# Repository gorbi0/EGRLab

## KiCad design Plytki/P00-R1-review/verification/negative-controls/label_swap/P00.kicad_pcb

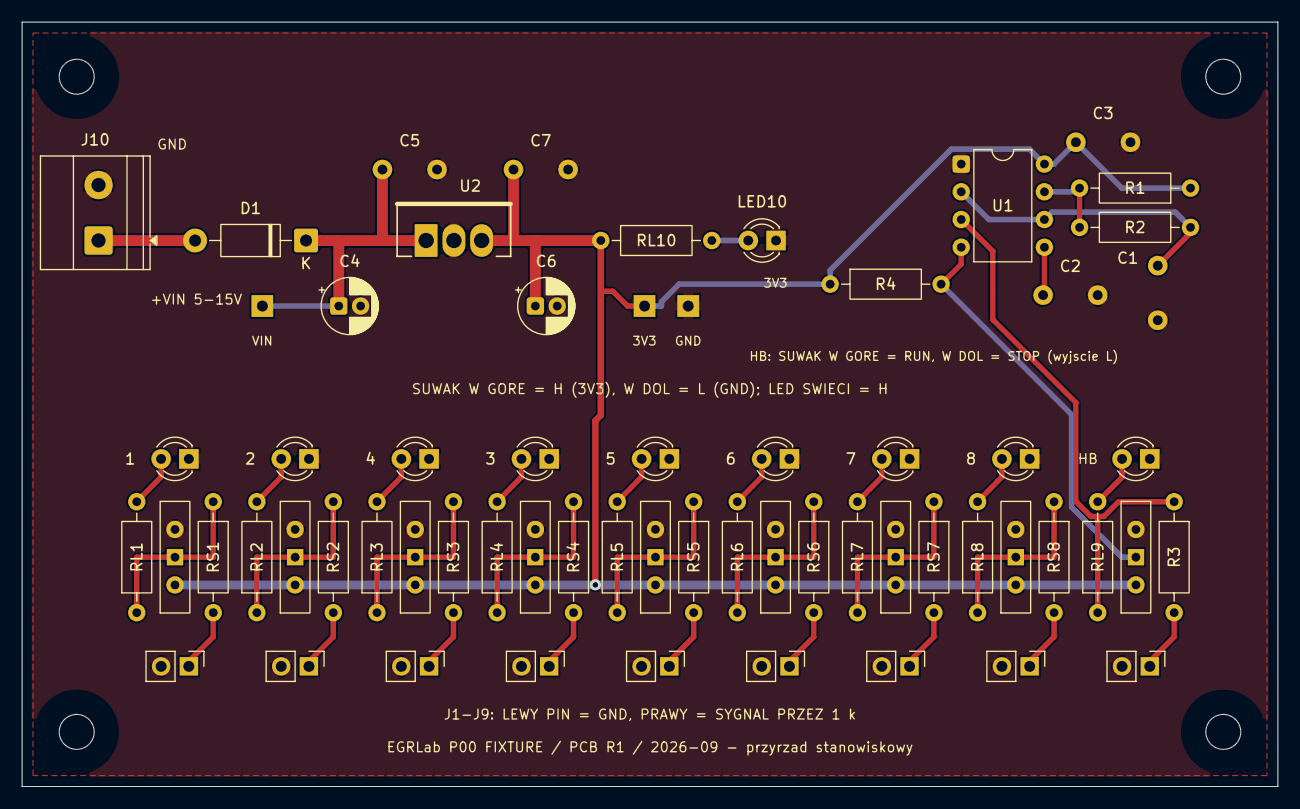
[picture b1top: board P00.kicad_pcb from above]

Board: 2 copper layers, 115.0 x 70.0 mm, 68 parts (0 on the bottom side), 36 nets.

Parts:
C1, C3, C5, C7: 100nF / X7R; C_Vishay_K15_H5_P5
C2: 10nF / X7R; C_Vishay_K15_H5_P5
C4: 10u / 50V; CP_Radial_D5.0mm_P2.00mm
C6: 22u / 16V; CP_Radial_D5.0mm_P2.00mm
D1: 1N5819; D_DO-41_SOD81_P10.16mm_Horizontal
H1, H2, H3, H4: M3 NPTH
J1: CH1 / pin header 1x2; PinHeader_1x02_P2.54mm_Vertical
J2: CH2 / pin header 1x2; PinHeader_1x02_P2.54mm_Vertical
J3: CH3 / pin header 1x2; PinHeader_1x02_P2.54mm_Vertical
J4: CH4 / pin header 1x2; PinHeader_1x02_P2.54mm_Vertical
J5: CH5 / pin header 1x2; PinHeader_1x02_P2.54mm_Vertical
J6: CH6 / pin header 1x2; PinHeader_1x02_P2.54mm_Vertical
J7: CH7 / pin header 1x2; PinHeader_1x02_P2.54mm_Vertical
J8: CH8 / pin header 1x2; PinHeader_1x02_P2.54mm_Vertical
J9: HEART / pin header 1x2; PinHeader_1x02_P2.54mm_Vertical
J10: VIN 5-15V / MKDS 2p; TerminalBlock_Phoenix_MKDS-1,5-2-5.08_1x02_P5.08mm_Horizont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
LED1: GREEN 3mm / CH1; LED_D3.0mm
LED2: GREEN 3mm / CH2; LED_D3.0mm
LED3: GREEN 3mm / CH3; LED_D3.0mm
LED4: GREEN 3mm / CH4; LED_D3.0mm
LED5: GREEN 3mm / CH5; LED_D3.0mm
LED6: GREEN 3mm / CH6; LED_D3.0mm
LED7: GREEN 3mm / CH7; LED_D3.0mm
LED8: GREEN 3mm / CH8; LED_D3.0mm
LED9: YELLOW 3mm / HEART; LED_D3.0mm
LED10: RED 3mm / 3V3; LED_D3.0mm
R1: 4K7 / 1%; R_Axial_DIN0207_L6.3mm_D2.5mm_P10.16mm_Horizontal
R2: 68K / 1%; R_Axial_DIN0207_L6.3mm_D2.5mm_P10.16mm_Horizontal
R3: 1K / 1%; R_Axial_DIN0207_L6.3mm_D2.5mm_P10.16mm_Horizontal
R4: 100K / 1%; R_Axial_DIN0207_L6.3mm_D2.5mm_P10.16mm_Horizontal
RL1, RL2, RL3, RL4, RL5, RL6, RL7, RL8, RL9, RL10: 1K / 1%; R_Axial_DIN0207_L6.3mm_D2.5mm_P10.16mm_Horizontal
RS1, RS2, RS3, RS4, RS5, RS6, RS7, RS8: 1K / 1%; R_Axial_DIN0207_L6.3mm_D2.5mm_P10.16mm_Horizontal
SW1: CH1 H/L; SW_Slide-03_Wuerth-WS-SLTV_10x2.5x6.4_P2.54mm
SW2: CH2 H/L; SW_Slide-03_Wuerth-WS-SLTV_10x2.5x6.4_P2.54mm
SW3: CH3 H/L; SW_Slide-03_Wuerth-WS-SLTV_10x2.5x6.4_P2.54mm
SW4: CH4 H/L; SW_Slide-03_Wuerth-WS-SLTV_10x2.5x6.4_P2.54mm
SW5: CH5 H/L; SW_Slide-03_Wuerth-WS-SLTV_10x2.5x6.4_P2.54mm
SW6: CH6 H/L; SW_Slide-03_Wuerth-WS-SLTV_10x2.5x6.4_P2.54mm
SW7: CH7 H/L; SW_Slide-03_Wuerth-WS-SLTV_10x2.5x6.4_P2.54mm
SW8: CH8 H/L; SW_Slide-03_Wuerth-WS-SLTV_10x2.5x6.4_P2.54mm
SW9: HEART RUN/STOP; SW_Slide-03_Wuerth-WS-SLTV_10x2.5x6.4_P2.54mm
TP1: V33; TestPad_1
TP2: GND; TestPad_1
TP3: VIN_P; TestPad_1
U1: TLC555CP; DIP-8_W7.62mm
U2: LM2937ET-3.3; TO220_3_P2.54_Drill1.4

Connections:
/P00_CTRL: C2.1, U1.5
/P00_DIS: R1.2, R2.1, U1.7
/P00_HEART: J9.1, R3.2
/P00_LED1: LED1.2, RL1.2
/P00_LED2: LED2.2, RL2.2
/P00_LED3: LED3.2, RL3.2
/P00_LED4: LED4.2, RL4.2
/P00_LED5: LED5.2, RL5.2
/P00_LED6: LED6.2, RL6.2
/P00_LED7: LED7.2, RL7.2
/P00_LED8: LED8.2, RL8.2
/P00_LED_HB: LED9.2, RL9.2
/P00_LED_PWR: LED10.2, RL10.2
/P00_OSC: R3.1, RL9.1, U1.3
/P00_OUT1: J1.1, RS1.2
/P00_OUT2: J2.1, RS2.2
/P00_OUT3: J3.1, RS3.2
/P00_OUT4: J4.1, RS4.2
/P00_OUT5: J5.1, RS5.2
/P00_OUT6: J6.1, RS6.2
/P00_OUT7: J7.1, RS7.2
/P00_OUT8: J8.1, RS8.2
/P00_RC: C1.1, R2.2, U1.2, U1.6
/P00_RESET: R4.2, SW9.1, U1.4
/P00_S1: RL1.1, RS1.1, SW1.1
/P00_S2: RL2.1, RS2.1, SW2.1
/P00_S3: RL3.1, RS3.1, SW3.1
/P00_S4: RL4.1, RS4.1, SW4.1
/P00_S5: RL5.1, RS5.1, SW5.1
/P00_S6: RL6.1, RS6.1, SW6.1
/P00_S7: RL7.1, RS7.1, SW7.1
/P00_S8: RL8.1, RS8.1, SW8.1
/P00_V33: C3.1, C6.1, C7.1, R1.1, R4.1, RL10.1, SW1.2, SW2.2, SW3.2, SW4.2, SW5.2, SW6.2, SW7.2, SW8.2, SW9.2, TP1.1, U1.8, U2.3
/P00_VIN: D1.2, J10.1
/P00_VIN_P: C4.1, C5.1, D1.1, TP3.1, U2.1
GND: C1.2, C2.2, C3.2, C4.2, C5.2, C6.2, C7.2, J1.2, J2.2, J3.2, J4.2, J5.2, J6.2, J7.2, J8.2, J9.2, J10.2, LED1.1, LED2.1, LED3.1, LED4.1, LED5.1, LED6.1, LED7.1, LED8.1, LED9.1, LED10.1, SW1.3, SW2.3, SW3.3, SW4.3, SW5.3, SW6.3, SW7.3, SW8.3, SW9.3, TP2.1, U1.1, U2.2
